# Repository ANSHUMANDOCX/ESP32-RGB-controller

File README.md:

# ESP32 WiFi RGB Controller
This is a controller for a 5050 12v RGB leds which is controlled via an Web interface using a ESP32.
### Basic working mechanism
these 5050 led strips are common anode so, using mosfets connected to each colour R G B we can controll the bright ness of each light which in turn will help us choose any coulour we want.

## Parts used
- ESP32 Wroom
- IRFZ44N N-channel Mosfets
- 12V Supply
- 5050 Common anode RGB leds

## Schematic PCB and CAD

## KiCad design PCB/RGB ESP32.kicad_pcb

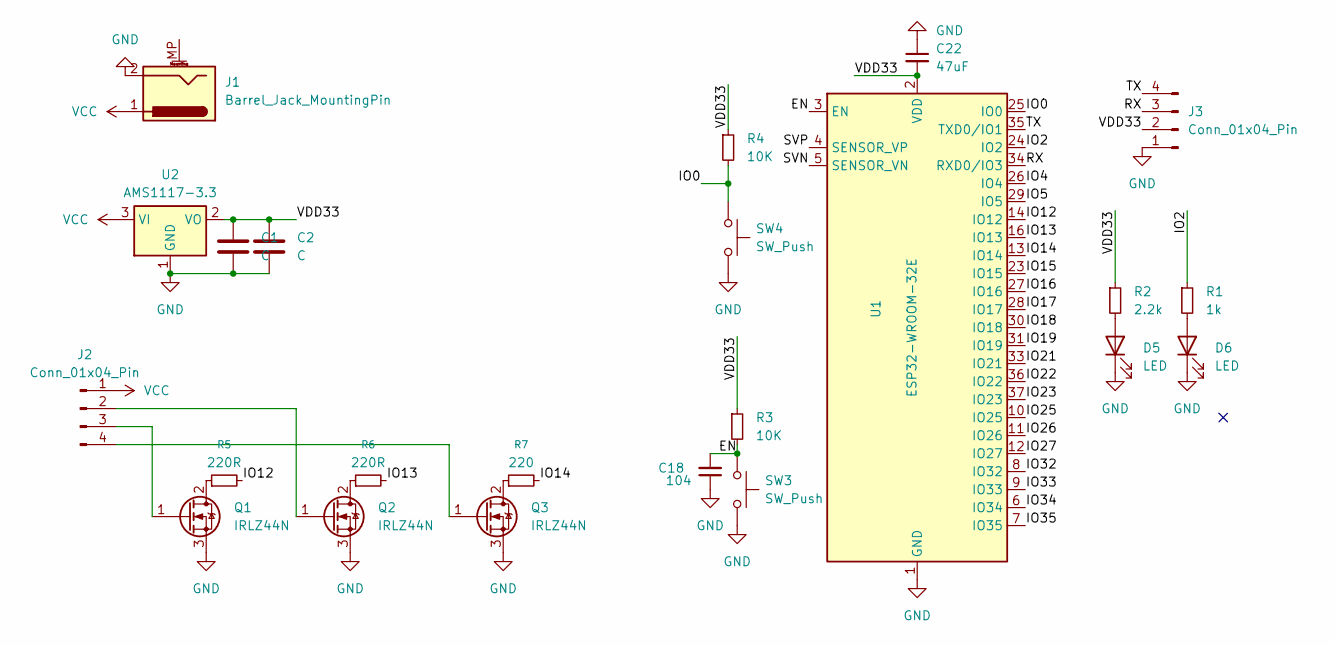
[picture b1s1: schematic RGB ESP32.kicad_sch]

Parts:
C1, C2: C; C_0603_1608Metric
C18: 104; C_0603_1608Metric_Pad1.08x0.95mm_HandSolder
C22: 47uF; C_0603_1608Metric_Pad1.08x0.95mm_HandSolder
D5, D6: LED; LED_0805_2012Metric_Pad1.15x1.40mm_HandSolder
J1: Barrel_Jack_MountingPin; BarrelJack_Kycon_KLDX-0202-xC_Horizontal
J2, J3: Conn_01x04_Pin; PinHeader_1x04_P2.54mm_Vertical
Q1, Q2, Q3: IRLZ44N; TO-220-3_Vertical
R1: 1k; R_0603_1608Metric_Pad0.98x0.95mm_HandSolder
R2: 2.2k; R_0603_1608Metric_Pad0.98x0.95mm_HandSolder
R3, R4: 10K; R_0603_1608Metric_Pad0.98x0.95mm_HandSolder
R5, R6: 220R; R_0603_1608Metric
R7: 220; R_0603_1608Metric
SW3, SW4: SW_Push; SW_Push_SPST_NO_Alps_SKRK
U1: ESP32-WROOM-32E; ESP32-WROOM-32D
U2: AMS1117-3.3; SOT-223-3_TabPin2

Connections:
/EN: C18.2, R3.2, SW3.1, U1.3 (EN)
/IO0: R4.2, SW4.1, U1.25 (IO0)
/IO2: R1.1, U1.24 (IO2)
/IO4: U1.26 (IO4)
/IO5: U1.29 (IO5)
/IO12: R5.2, U1.14 (IO12)
/IO13: R6.2, U1.16 (IO13)
/IO14: R7.2, U1.13 (IO14)
/IO15: U1.23 (IO15)
/IO16: U1.27 (IO16)
/IO17: U1.28 (IO17)
/IO18: U1.30 (IO18)
/IO19: U1.31 (IO19)
/IO21: U1.33 (IO21)
/IO22: U1.36 (IO22)
/IO23: U1.37 (IO23)
/IO25: U1.10 (IO25)
/IO26: U1.11 (IO26)
/IO27: U1.12 (IO27)
/IO32: U1.8 (IO32)
/IO33: U1.9 (IO33)
/IO34: U1.6 (IO34)
/IO35: U1.7 (IO35)
/RX: J3.3, U1.34 (RXD0/IO3)
/SVN: U1.5 (SENSOR_VN)
/SVP: U1.4 (SENSOR_VP)
/TX: J3.4, U1.35 (TXD0/IO1)
/VDD33: C1.1, C2.1, C22.2, J3.2, R2.1, R3.1, R4.1, U1.2 (VDD), U2.2 (VO)
GND: C1.2, C2.2, C18.1, C22.1, D5.1 (K), D6.1 (K), J1.2, J3.1, Q1.3 (S), Q2.3 (S), Q3.3 (S), SW3.2, SW4.2, U1.1 (GND), U1.15 (GND), U1.38 (GND), U1.39 (GND), U2.1 (GND)
unnamed: D5.2 (A), R2.2
unnamed: D6.2 (A), R1.2
unnamed: J2.2, Q2.1 (G)
unnamed: J2.3, Q1.1 (G)
unnamed: J2.4, Q3.1 (G)
unnamed: Q1.2 (D), R5.1
unnamed: Q2.2 (D), R6.1
unnamed: Q3.2 (D), R7.1
VCC: J1.1, J2.1, U2.3 (VI)

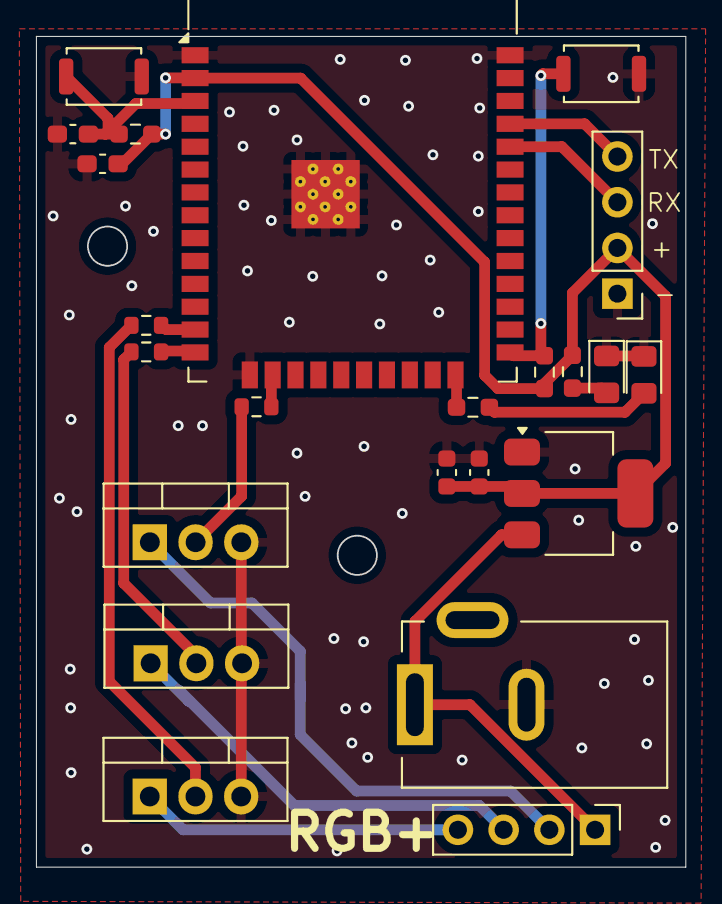
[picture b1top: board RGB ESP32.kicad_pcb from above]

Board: 2 copper layers, 36.0 x 46.1 mm, 23 parts (0 on the bottom side), 19 nets.

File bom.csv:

Designator,Footprint,Quantity,Value,LCSC Part #
"C1, C2",0603,2,C,
C18,0603,1,104,
C22,0603,1,47uF,
"D5, D6",0805,2,LED,
J1,BarrelJack_Kycon_KLDX-0202-xC_Horizontal,1,Barrel_Jack_MountingPin,
"J2, J3",PinHeader_1x04_P2.54mm_Vertical,2,Conn_01x04_Pin,
"Q1, Q2, Q3",TO-220-3_Vertical,3,IRLZ44N,
R1,0603,1,1k,
R2,0603,1,2.2k,
"R3, R4",0603,2,10K,
"R5, R6",0603,2,220R,
R7,0603,1,220,
"SW3, SW4",SW_Push_SPST_NO_Alps_SKRK,2,SW_Push,
U1,ESP32-WROOM-32D,1,ESP32-WROOM-32E,
U2,SOT-223-3_TabPin2,1,AMS1117-3.3,
